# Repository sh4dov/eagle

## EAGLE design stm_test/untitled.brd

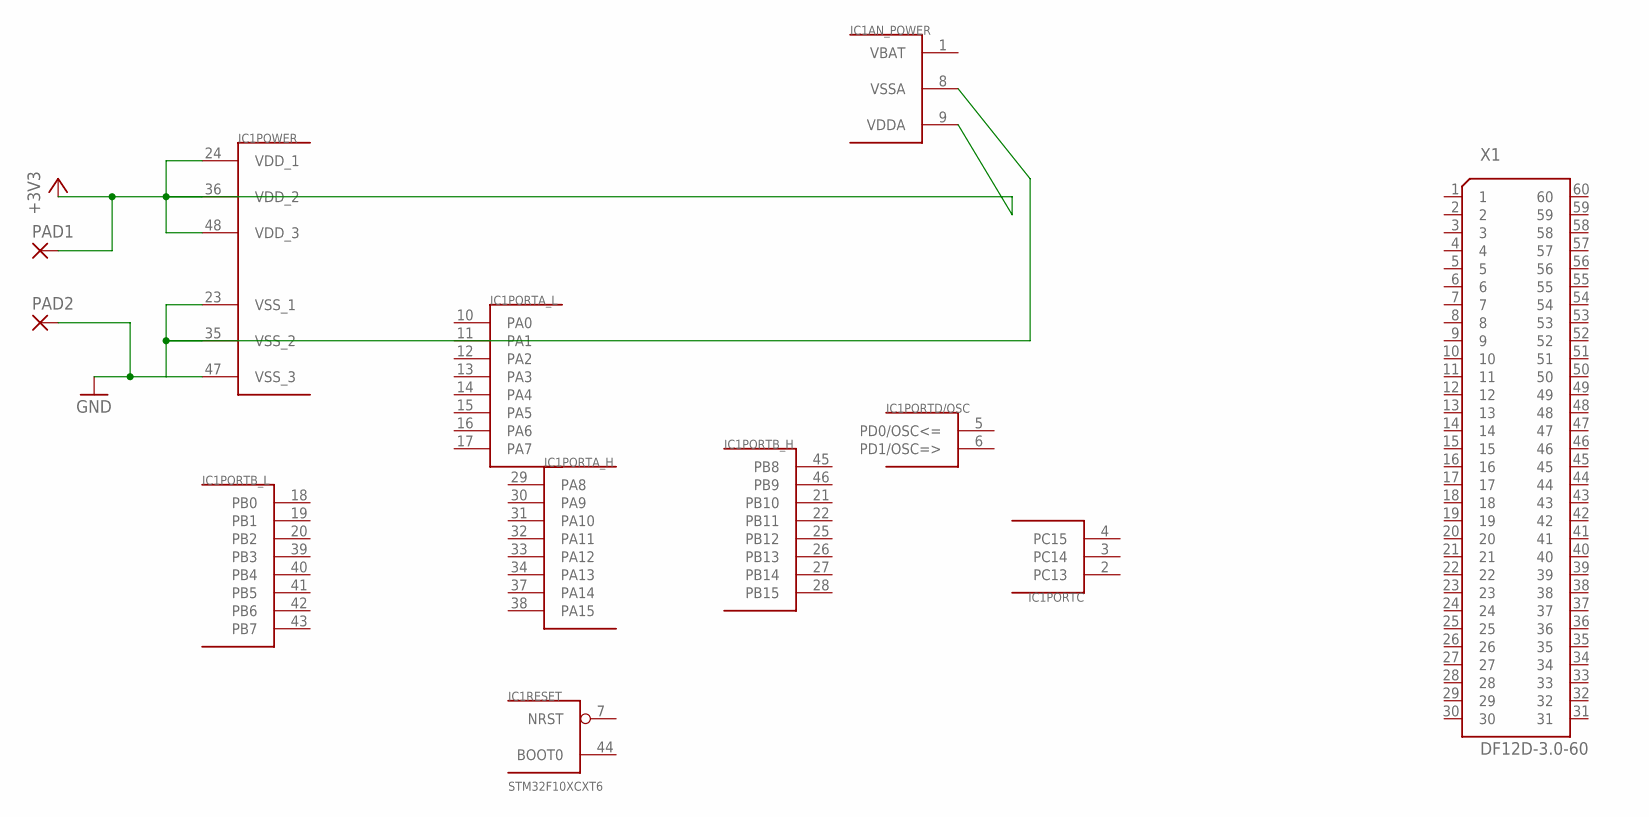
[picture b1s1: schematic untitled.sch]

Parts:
IC1: STM32F10XCXT6; TQFP48
PAD1, PAD2: 1,6/0,8
X1: DF12D-3.0-60; DF12-3.0-60

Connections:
+3V3: IC1.9 (VDDA), IC1.24 (VDD_1), IC1.36 (VDD_2), IC1.48 (VDD_3), PAD1.1
GND: IC1.8 (VSSA), IC1.23 (VSS_1), IC1.35 (VSS_2), IC1.47 (VSS_3), PAD2.1
VBAT: IC1.1 (VBAT)

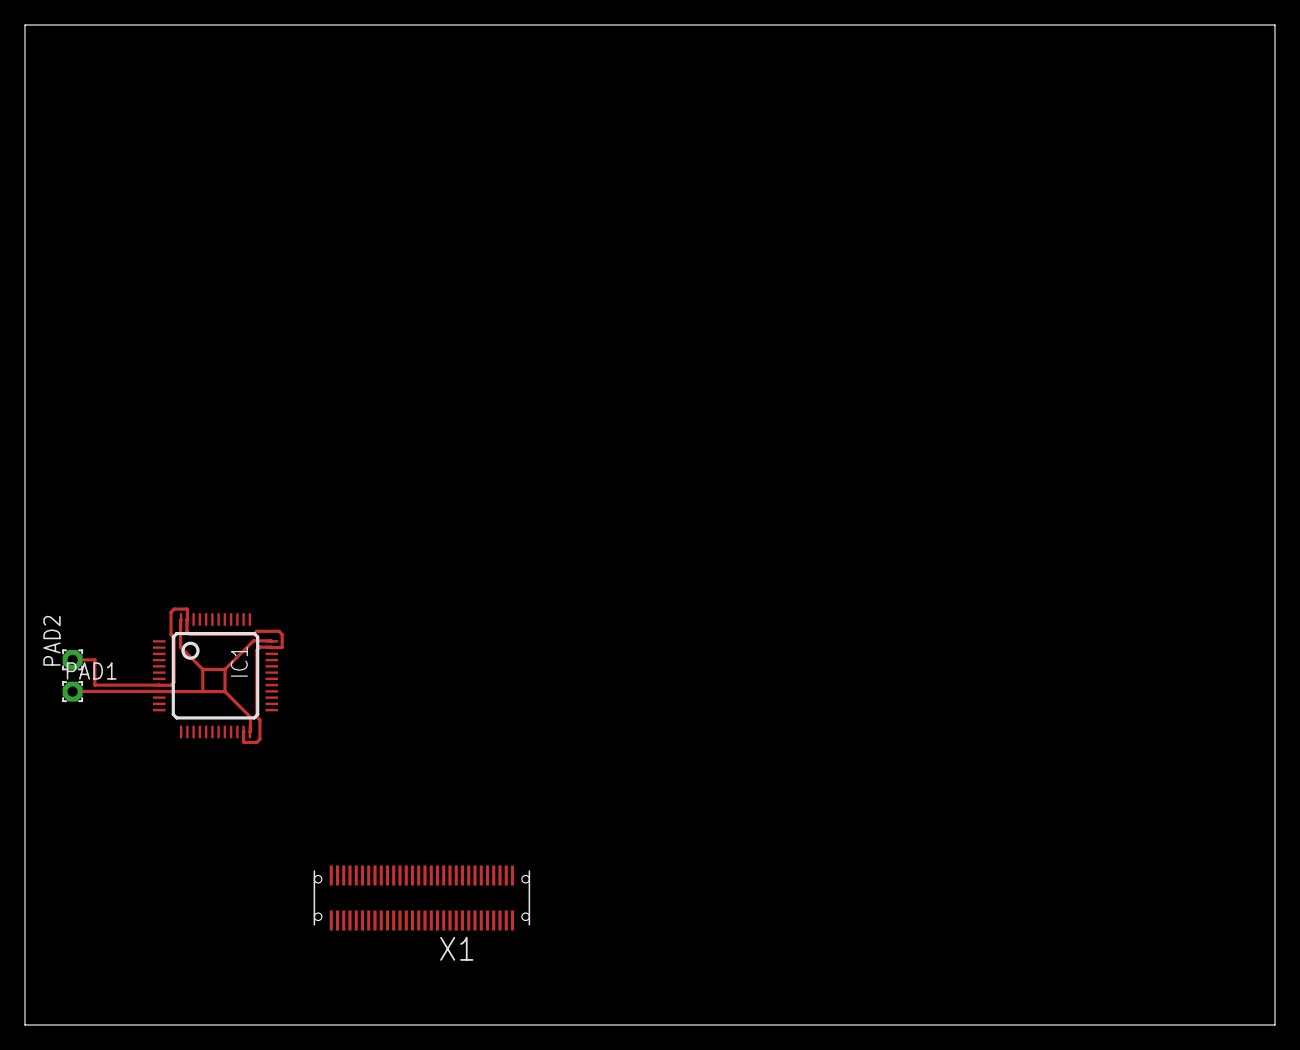
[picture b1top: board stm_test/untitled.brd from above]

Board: 2 copper layers, 100.0 x 80.0 mm, 4 parts (0 on the bottom side), 2 nets.

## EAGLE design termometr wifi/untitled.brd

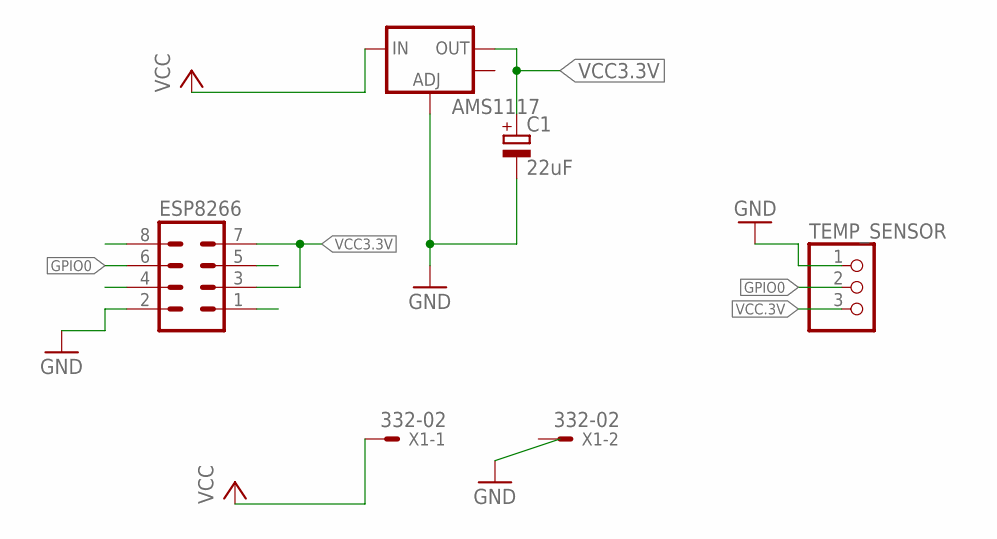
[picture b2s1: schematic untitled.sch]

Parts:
AMS1117: V_REG_LM1117SOT223; SOT223
C1: 22uF; E1,8-4
ESP8266: MA04-2
TEMP_SENSOR: PINHD-1X3; 1X03
X1: 332-02

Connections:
GND: AMS1117.1 (ADJ), C1.-, ESP8266.2, TEMP_SENSOR.1
GPIO0: ESP8266.6, TEMP_SENSOR.2
VCC: AMS1117.3 (IN), X1.1
VCC3.3V: AMS1117.2 (OUT), C1.+, ESP8266.3, ESP8266.7
VCC.3V: TEMP_SENSOR.3

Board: 2 copper layers, 5 parts (0 on the bottom side), 4 nets, no tracks yet.

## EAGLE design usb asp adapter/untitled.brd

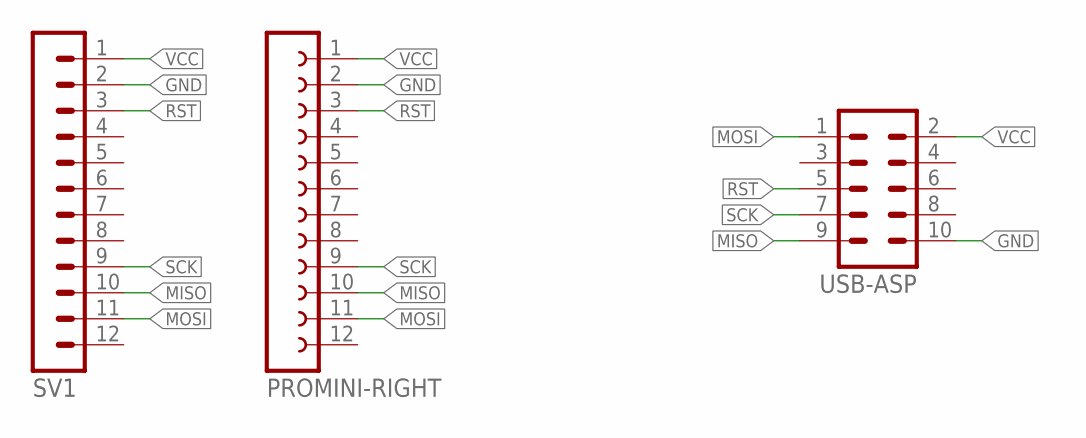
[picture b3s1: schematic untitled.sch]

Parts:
PROMINI-RIGHT: FE12-1; FE12
SV1: MA12-1
USB-ASP: MA05-2

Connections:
GND: PROMINI-RIGHT.2, SV1.2, USB-ASP.10
MISO: PROMINI-RIGHT.10, SV1.10, USB-ASP.9
MOSI: PROMINI-RIGHT.11, SV1.11, USB-ASP.1
RST: PROMINI-RIGHT.3, SV1.3, USB-ASP.5
SCK: PROMINI-RIGHT.9, SV1.9, USB-ASP.7
VCC: PROMINI-RIGHT.1, SV1.1, USB-ASP.2

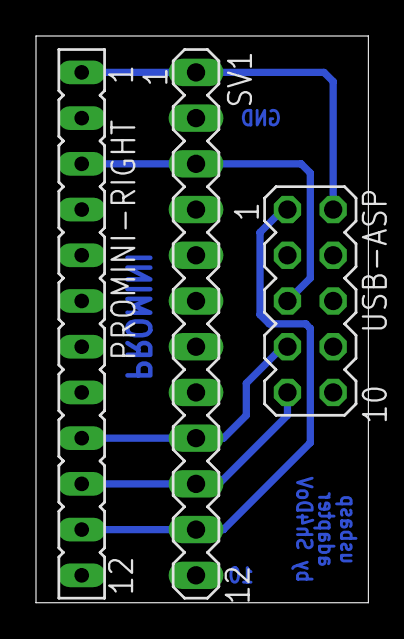
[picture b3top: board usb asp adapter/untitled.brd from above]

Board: 2 copper layers, 18.5 x 31.5 mm, 3 parts (0 on the bottom side), 6 nets.

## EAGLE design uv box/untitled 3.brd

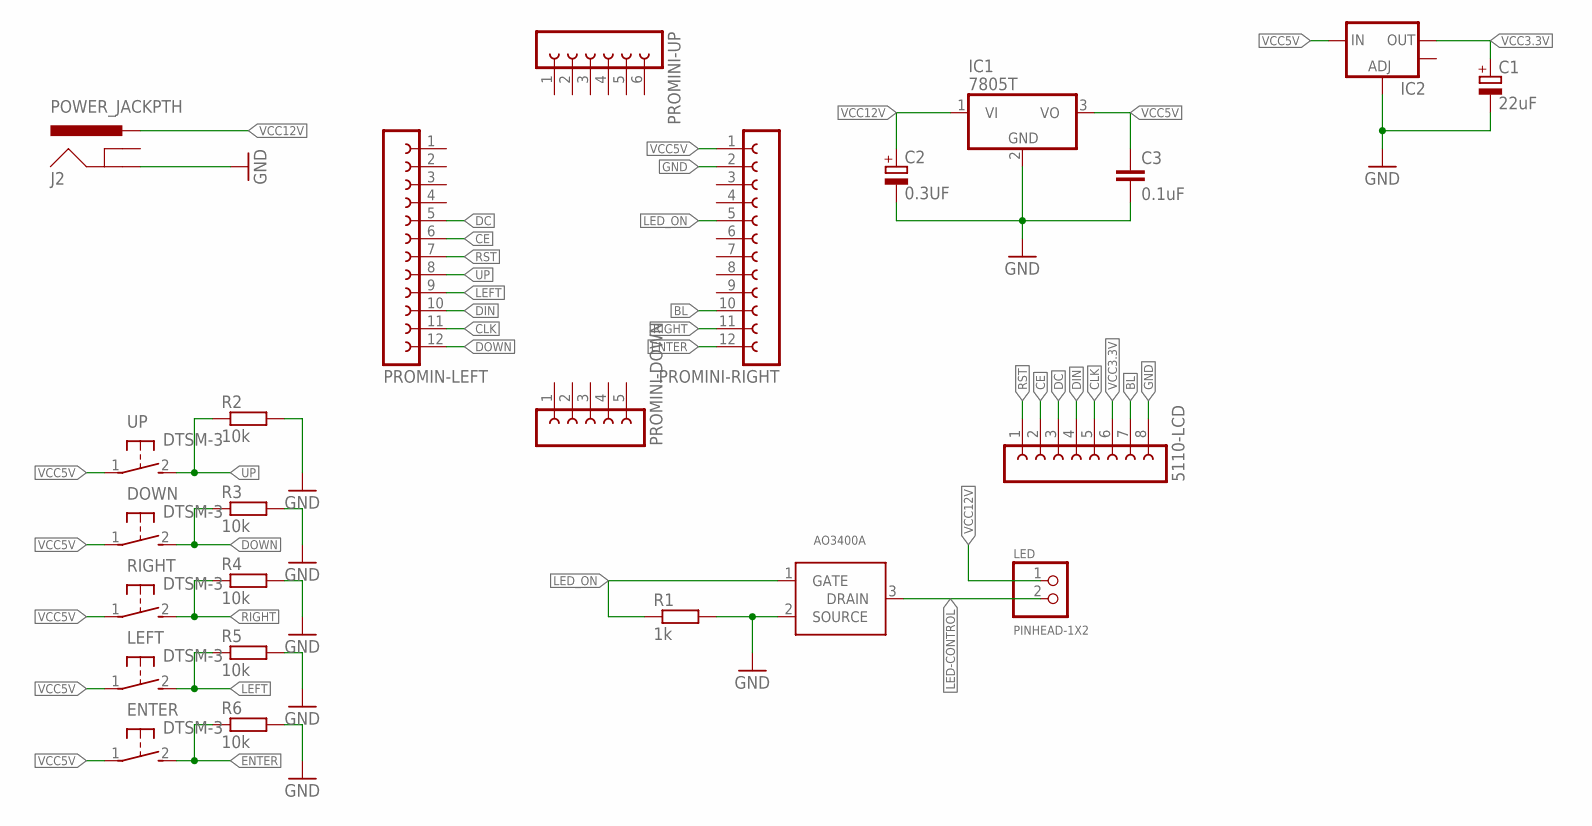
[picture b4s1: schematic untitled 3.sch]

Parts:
5110-LCD: FE08-1; FE08
C1: 22uF; E2-5
C2: 0.3UF; E5-5
C3: 0.1uF; C050-025X075
DOWN: DTSM-3
ENTER: DTSM-3
IC1: 7805T; TO220H
IC2: V_REG_LM1117SOT223; SOT223
J2: POWER_JACKPTH; POWER_JACK_PTH
LED: PINHEAD-1X2; PIHEAD-1X2
LEFT: DTSM-3
PROMIN-LEFT: FE12-1; FE12
PROMINI-DOWN: FE05-1
PROMINI-RIGHT: FE12-1; FE12
PROMINI-UP: FE06-1; FE06
R1: 1k; R1206
R2, R3, R4, R5, R6: 10k; R1206
RIGHT: DTSM-3
U$1: AO3400A; SOT-23
UP: DTSM-3

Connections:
BL: 5110-LCD.7, PROMINI-RIGHT.10
CE: 5110-LCD.2, PROMIN-LEFT.6
CLK: 5110-LCD.5, PROMIN-LEFT.11
DC: 5110-LCD.3, PROMIN-LEFT.5
DIN: 5110-LCD.4, PROMIN-LEFT.10
DOWN: DOWN.2, PROMIN-LEFT.12, R3.1
ENTER: ENTER.2, PROMINI-RIGHT.12, R6.1
GND: 5110-LCD.8, C1.-, C2.-, C3.2, IC1.2 (GND), IC2.1 (ADJ), J2.GND, PROMINI-RIGHT.2, R1.2, R2.2, R3.2, R4.2, R5.2, R6.2, U$1.2 (SOURCE)
LED-CONTROL: LED.2, U$1.3 (DRAIN)
LED_ON: PROMINI-RIGHT.5, R1.1, U$1.1 (GATE)
LEFT: LEFT.2, PROMIN-LEFT.9, R5.1
RIGHT: PROMINI-RIGHT.11, R4.1, RIGHT.2
RST: 5110-LCD.1, PROMIN-LEFT.7
UP: PROMIN-LEFT.8, R2.1, UP.2
VCC3.3V: 5110-LCD.6, C1.+, IC2.2 (OUT)
VCC5V: C3.1, DOWN.1, ENTER.1, IC1.3 (VO), IC2.3 (IN), LEFT.1, PROMINI-RIGHT.1, RIGHT.1, UP.1
VCC12V: C2.+, IC1.1 (VI), J2.PWR, LED.1

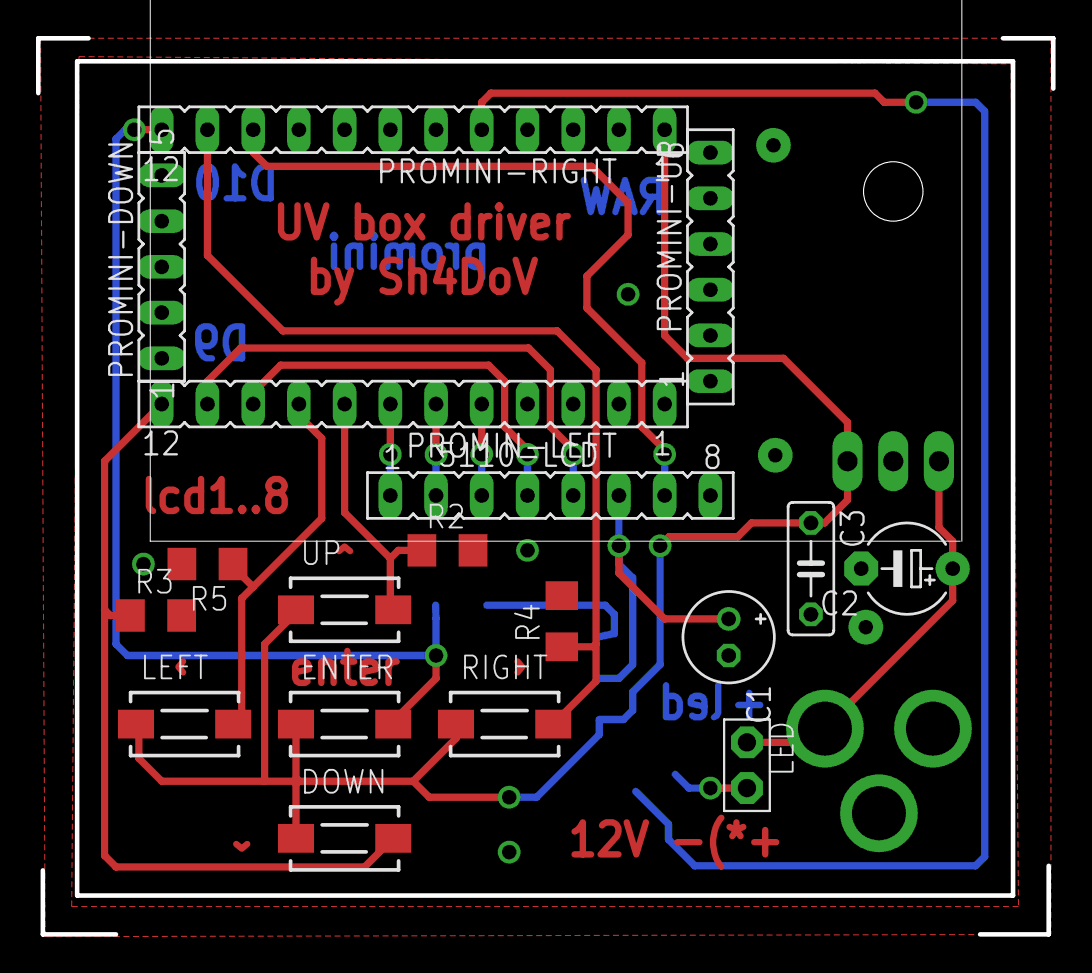
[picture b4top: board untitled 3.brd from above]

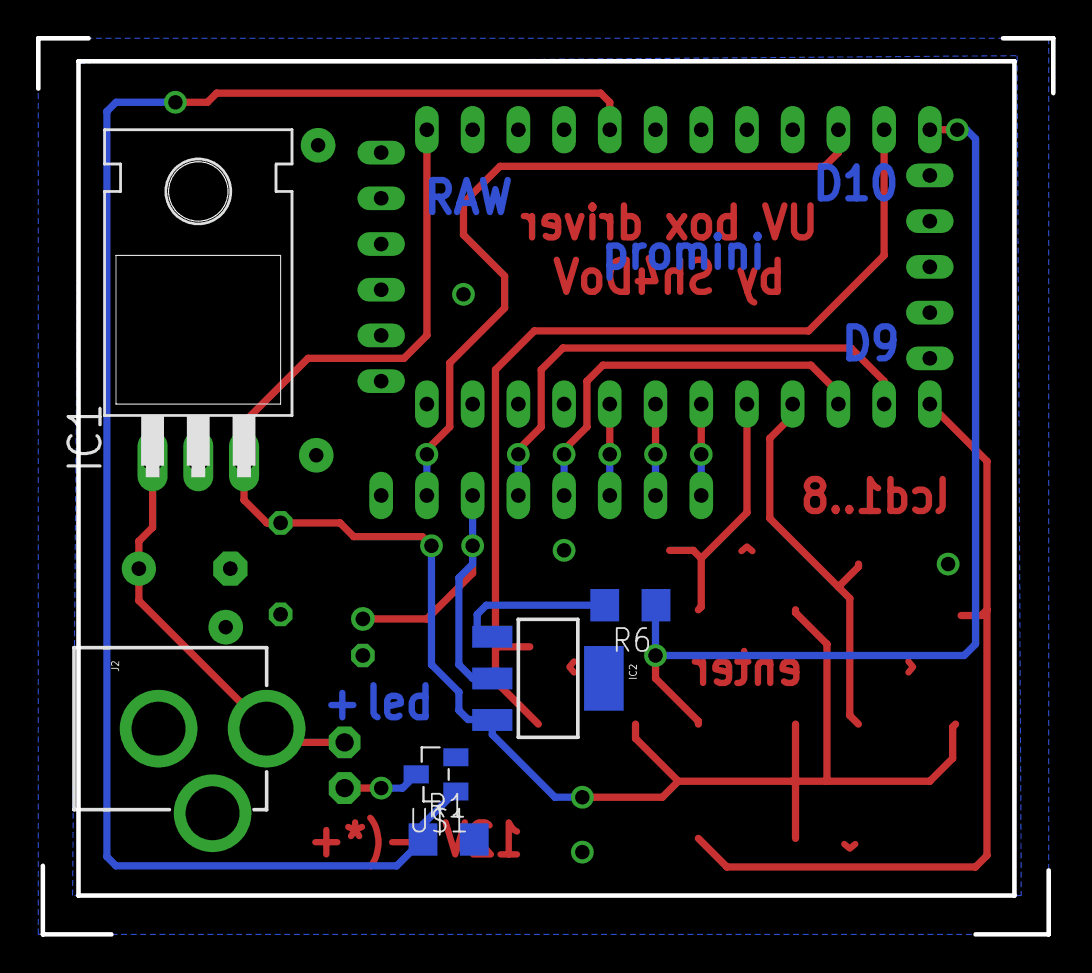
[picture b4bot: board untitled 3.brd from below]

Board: 2 copper layers, 56.4 x 49.8 mm, 24 parts (6 on the bottom side), 17 nets.

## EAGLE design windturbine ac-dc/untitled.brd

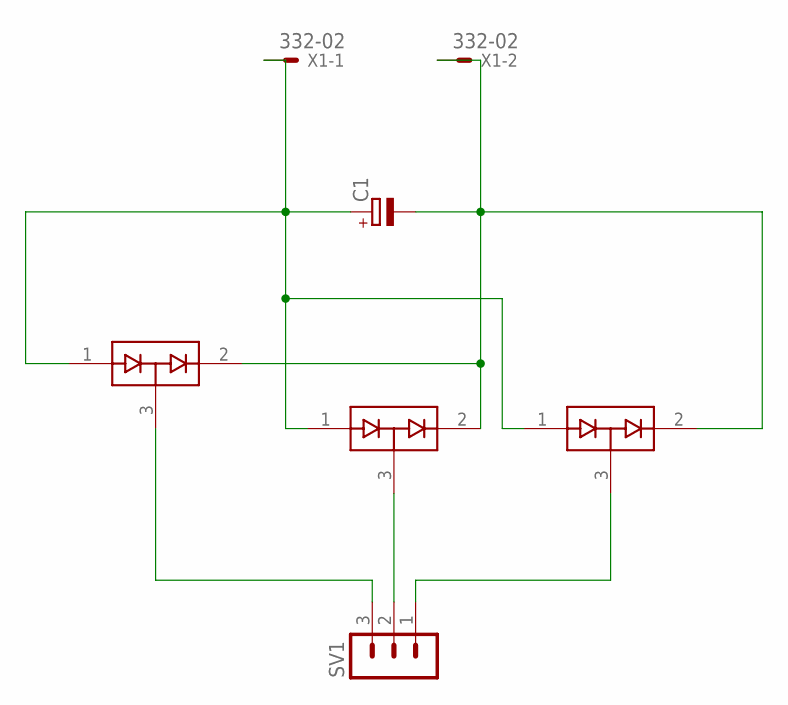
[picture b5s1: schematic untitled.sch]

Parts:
C1: CPOL-EUE2-5; E2-5
D1, D2, D3: BAV99; SOT23-3
SV1: MA03-1
X1: 332-02

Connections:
unnamed: D1.3 (COM), SV1.3
unnamed: D2.3 (COM), SV1.2
unnamed: D3.3 (COM), SV1.1
unnamed: C1.+, D1.1 (A1), D2.1 (A1), D3.1 (A1), X1.1
unnamed: C1.-, D1.2 (C2), D2.2 (C2), D3.2 (C2), X1.2

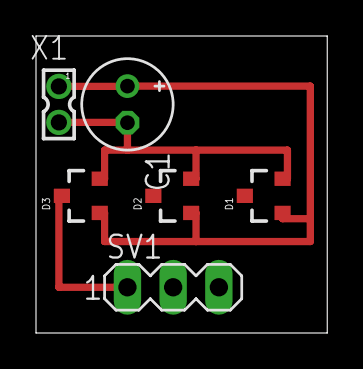
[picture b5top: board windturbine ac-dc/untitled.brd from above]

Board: 2 copper layers, 16.2 x 16.5 mm, 6 parts (0 on the bottom side), 5 nets.

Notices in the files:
parts and their libraries:
SparkFun-PowerIC: Licensing: Creative Commons ShareAlike 4.0 International - https://creativecommons.org/licenses/by-sa/4.0
